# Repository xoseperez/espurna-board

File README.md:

View this project on [CADLAB.io](https://cadlab.io/node/890). 

# ESPurna Boards

## ESPurna-H

The ESPurna-H board is a custom ESP8266-based smart wall switch. It's singularity is that it's meant to be embedded into the wall behind a standard wall switch, replacing the mechanic switch with a wifi-enabled smart switch.

The board is based on the HLW8012 power monitor IC, the same the Sonoff POW uses.

It features:

* SPDT 10A relay with **NO and NC connections** brought out
* Connections for **external button and notification LED**
* HLW8012 chip for **power monitoring**
* 50x50mm low profile form factor to fit in the wall switch hole

## Bill of materials

|Item|Location(s)|Buy|Required|Optional <sup>H</sup>|CPU <sup>units</sup>|Total|Total <sup>H</sup>|
|---|---|---|---|---|---|---|---|
|Tinkerman ESPurna-H PCB||[OSH Park](https://oshpark.com/shared_projects/lxVzIaBY)|1||6.50€ <sup>3</sup>|6.50€||
|Ai-Thinker ESP12F|ESP-12|[Aliexpress](http://s.click.aliexpress.com/e/mUZjemI) / [Ebay](https://rover.ebay.com/rover/1/711-53200-19255-0/1?icep_id=114&ipn=icep&toolid=20004&campid=5338044841&mpre=http%3A%2F%2Fwww.ebay.com%2Fitm%2FESP8266-Remote-Serial-Port-WIFI-Transceiver-Wireless-Module-Esp-12F-AP-STA-%2F272408386985%3Fhash%3Ditem3f6cce1da9%3Ag%3ArywAAOSwZJBX-7RV)|1||2.10€ <sup>5</sup>|2.10€||
|Hi-Link HLK-PM01|HLK-PM01|[Aliexpress](http://s.click.aliexpress.com/e/yzVBurN) / [Ebay](https://rover.ebay.com/rover/1/711-53200-19255-0/1?icep_id=114&ipn=icep&toolid=20004&campid=5338044841&mpre=http%3A%2F%2Fwww.ebay.com%2Fitm%2FHousehold-Switch-Hlk-Pm01-Ac-Dc-220V-To-5V-Step-Down-Power-Supply-Module-New-I-F-%2F262910032033%3Fhash%3Ditem3d36a8b8a1%3Ag%3A8gwAAOSwal5YH5sM)|1||2.16€ <sup>5</sup>|2.16€||
|Songle SRD-05VDC-SL-C||[Aliexpress](http://s.click.aliexpress.com/e/6Au7qf2) / [Ebay](https://rover.ebay.com/rover/1/711-53200-19255-0/1?icep_id=114&ipn=icep&toolid=20004&campid=5338044841&mpre=http%3A%2F%2Fwww.ebay.com%2Fitm%2F1pcs-SRD-05VDC-SL-C-5V-DC-SONGLE-Power-Relay-SRD-05VDC-SL-C-PCB-Type-%2F262148054761%3Fhash%3Ditem3d093ddee9%3Ag%3A9VEAAOxykVNRq~7c)|1||0.39€ <sup>3</sup>|0.39€||
|AMS1117-3.3|IC1|[Aliexpress](http://s.click.aliexpress.com/e/uj6iuNv) / [Ebay](https://rover.ebay.com/rover/1/711-53200-19255-0/1?icep_id=114&ipn=icep&toolid=20004&campid=5338044841&mpre=http%3A%2F%2Fwww.ebay.com%2Fitm%2FNew-10pcs-AMS1117-LM1117-3-3V-1A-SOT-223-Voltage-Regulator-NT00206-Ship-Today-%2F112049991237%3Fhash%3Ditem1a16b32e45%3Ag%3AqV8AAOSw14xWNwXc)|1||0.03€ <sup>50</sup>|0.03€||
|HLW8012|IC4|[Aliexpress](http://s.click.aliexpress.com/e/Fq7URjq)||1|0.72€ <sup>20</sup>||0.72€|
|SF70E 73C thermal fuse|F1|[Aliexpress](http://s.click.aliexpress.com/e/Fq7MFIQ)|1||1.20€ <sup>5</sup>|1.20€||
|Fuse holder|FUSE|[Aliexpress](http://s.click.aliexpress.com/e/uBMfQzR)|1||0.06€ <sup>100</sup>|0.06€||
|500mA 250V fuse|FUSE|[Aliexpress](http://s.click.aliexpress.com/e/Rj2jYB6)|1||0.05€ <sup>100</sup>|0.05€||
|Varistor 270V|VARISTOR|[Aliexpress](http://s.click.aliexpress.com/e/bUjIA2Z)|1||0.18€ <sup>20</sup>|0.18€||
|Push button|RESET|[Aliexpress](http://s.click.aliexpress.com/e/Nzrf6aa)|1||0.02€ <sup>100</sup>|0.02€||
|1N4148 SMD Diode|D3|[Aliexpress](http://s.click.aliexpress.com/e/i2nayrB)|1||0.04€ <sup>100</sup>|0.04€||
|2N7002 SOT-223 N-Mosfet|Q2, Q3, Q4|[Aliexpress](http://s.click.aliexpress.com/e/yFQnA2J)|2|1|0.05€ <sup>50</sup>|0.10€|0.05€|
|10uF 0805 tantalum capacitor|C11, C12||2||0.01€ <sup>100</sup>|0.02€||
|100nF 0805 ceramic capacitor|C21, C22, C43, C45||2|2|0.01€ <sup>100</sup>|0.02€|0.02€|
|33nF 0805 ceramic capacitor|C41, C42|||2|0.01€ <sup>100</sup>||0.02€|
|1uF 0805 ceramic capacitor|C44|||1|0.01€ <sup>100</sup>||0.01€|
|0.001 2512 Ohm resistor|R41|[Aliexpress](http://s.click.aliexpress.com/e/fIaA6QB)||1|0.03€ <sup>10</sup>||0.03€|
|0 Ohm 1206 resistor|R42|[Aliexpress](http://s.click.aliexpress.com/e/jEAqfqb)||1|0.01€ <sup>500</sup>||0.01€|
|22Ohm 0805 resistor|R27||1||0.01€ <sup>100</sup>|0.01€||
|300Ohm 0805 resistor|R28||1||0.01€ <sup>100</sup>|0.01€||
|1KOhm 0805 resistor|R31, R43, R44, R50||1|3|0.01€ <sup>100</sup>|0.01€|0.03€|
|10KOhm 0805 resistor|R21, R22, R23, R24,<br />R25, R26, R32, R45,<br />R47, R49||7|3|0.01€ <sup>100</sup>|0.07€|0.03€|
|15KOhm 0805 resistor|R46, R48|||2|0.01€ <sup>100</sup>||0.02€|
|470KOhm 0805 resistor|R51, R52, R53, R54,<br />R55|||5|0.01€ <sup>100</sup>||0.05€|
|2 positions 5mm screw terminal||[Aliexpress](http://s.click.aliexpress.com/e/a2fqnM7)|1||0.06€ <sup>100</sup>|0.06€||
|3 positions 5mm screw terminal||[Aliexpress](http://s.click.aliexpress.com/e/Vjaa2RB)|1||0.07€ <sup>100</sup>|0.07€||
|5x2 position male header|||1||0.01€ <sup>100</sup>|0.01€||
|**Total**||||||13.11€|0.97€|

* (H) Optional, only required for power monitor.
* (units) Minimum quantity for the stated price.
* Prices are based on the cheapest option, usually Aliexpress.
* Check the schematic (image or eagle file) for relation between parts and values.

## Firmware

NOTE: PLEASE NOTE THAT IT IS A REQUIREMENT OF THE HLW8012 POWER MONITOR CHIP TO TIE THE POWER LINE TO THE CIRCUIT GROUND. THIS MEANS THAT YOU SHOULD NEVER EVER CONNECT THE BOARD GROUND TO YOUR COMPUTER WHILE CONNECTED TO MAINS. NEVER EVER FLASH THE BOARD WHILE CONNECTED TO MAINS!!

The ESPurna board is named after the [ESPurna firmware](https://bitbucket.org/xoseperez/espurna) which features:

* Support for multiple ESP8266-based boards (check list)
* Support for up to 5 different network configurations
* Support for different types of switches and different options (pulses, synchronization,..)
* **MQTT** enabled
* **Alexa integration** using the FauxmoESP Library
* **Domoticz** integration via MQTT
* **Home Assistant** integration via MQTT
* Support for different **sensors** (DHT22, DS18B20, HLW8012, current sensors, analog sensors,...)
* Fast asynchronous **HTTP Server**
* Backup and restore settings option
* Upgrade firmware from the web interface
* **REST API** (enable/disable from web interface)
* **Over-The-Air** (OTA) updates
* ... and much more

## Open Hardware

Hardware designs (schematics and CAD) files are licensed under the [Creative Commons Attribution-ShareAlike 3.0 Unported License](http://creativecommons.org/licenses/by-sa/3.0/) and follow the terms of the [OSHW (Open-source hardware) Statement of Principles 1.0.](http://freedomdefined.org/OSHW)

## Disclaimer

THIS PRODUCT IS TARGETED TO EXPERIENCED USERS AT THEIR OWN RISK. THIS PRODUCT IS MEANT TO BE USED PLUGGED TO MAINS AND IT REQUIRES A DEEP UNDERSTANDING OF THE PERILS OF HIGH VOLTAGE ON HUMAN LIFE.

TO THE FULLEST EXTENT PERMISSIBLE BY THE APPLICABLE LAW, I HEREBY DISCLAIM ANY AND ALL RESPONSIBILITY, RISK, LIABILITY AND DAMAGES ARISING OUT OF DEATH OR PERSONAL INJURY RESULTING FROM ASSEMBLY OR OPERATION OF THIS PRODUCT.

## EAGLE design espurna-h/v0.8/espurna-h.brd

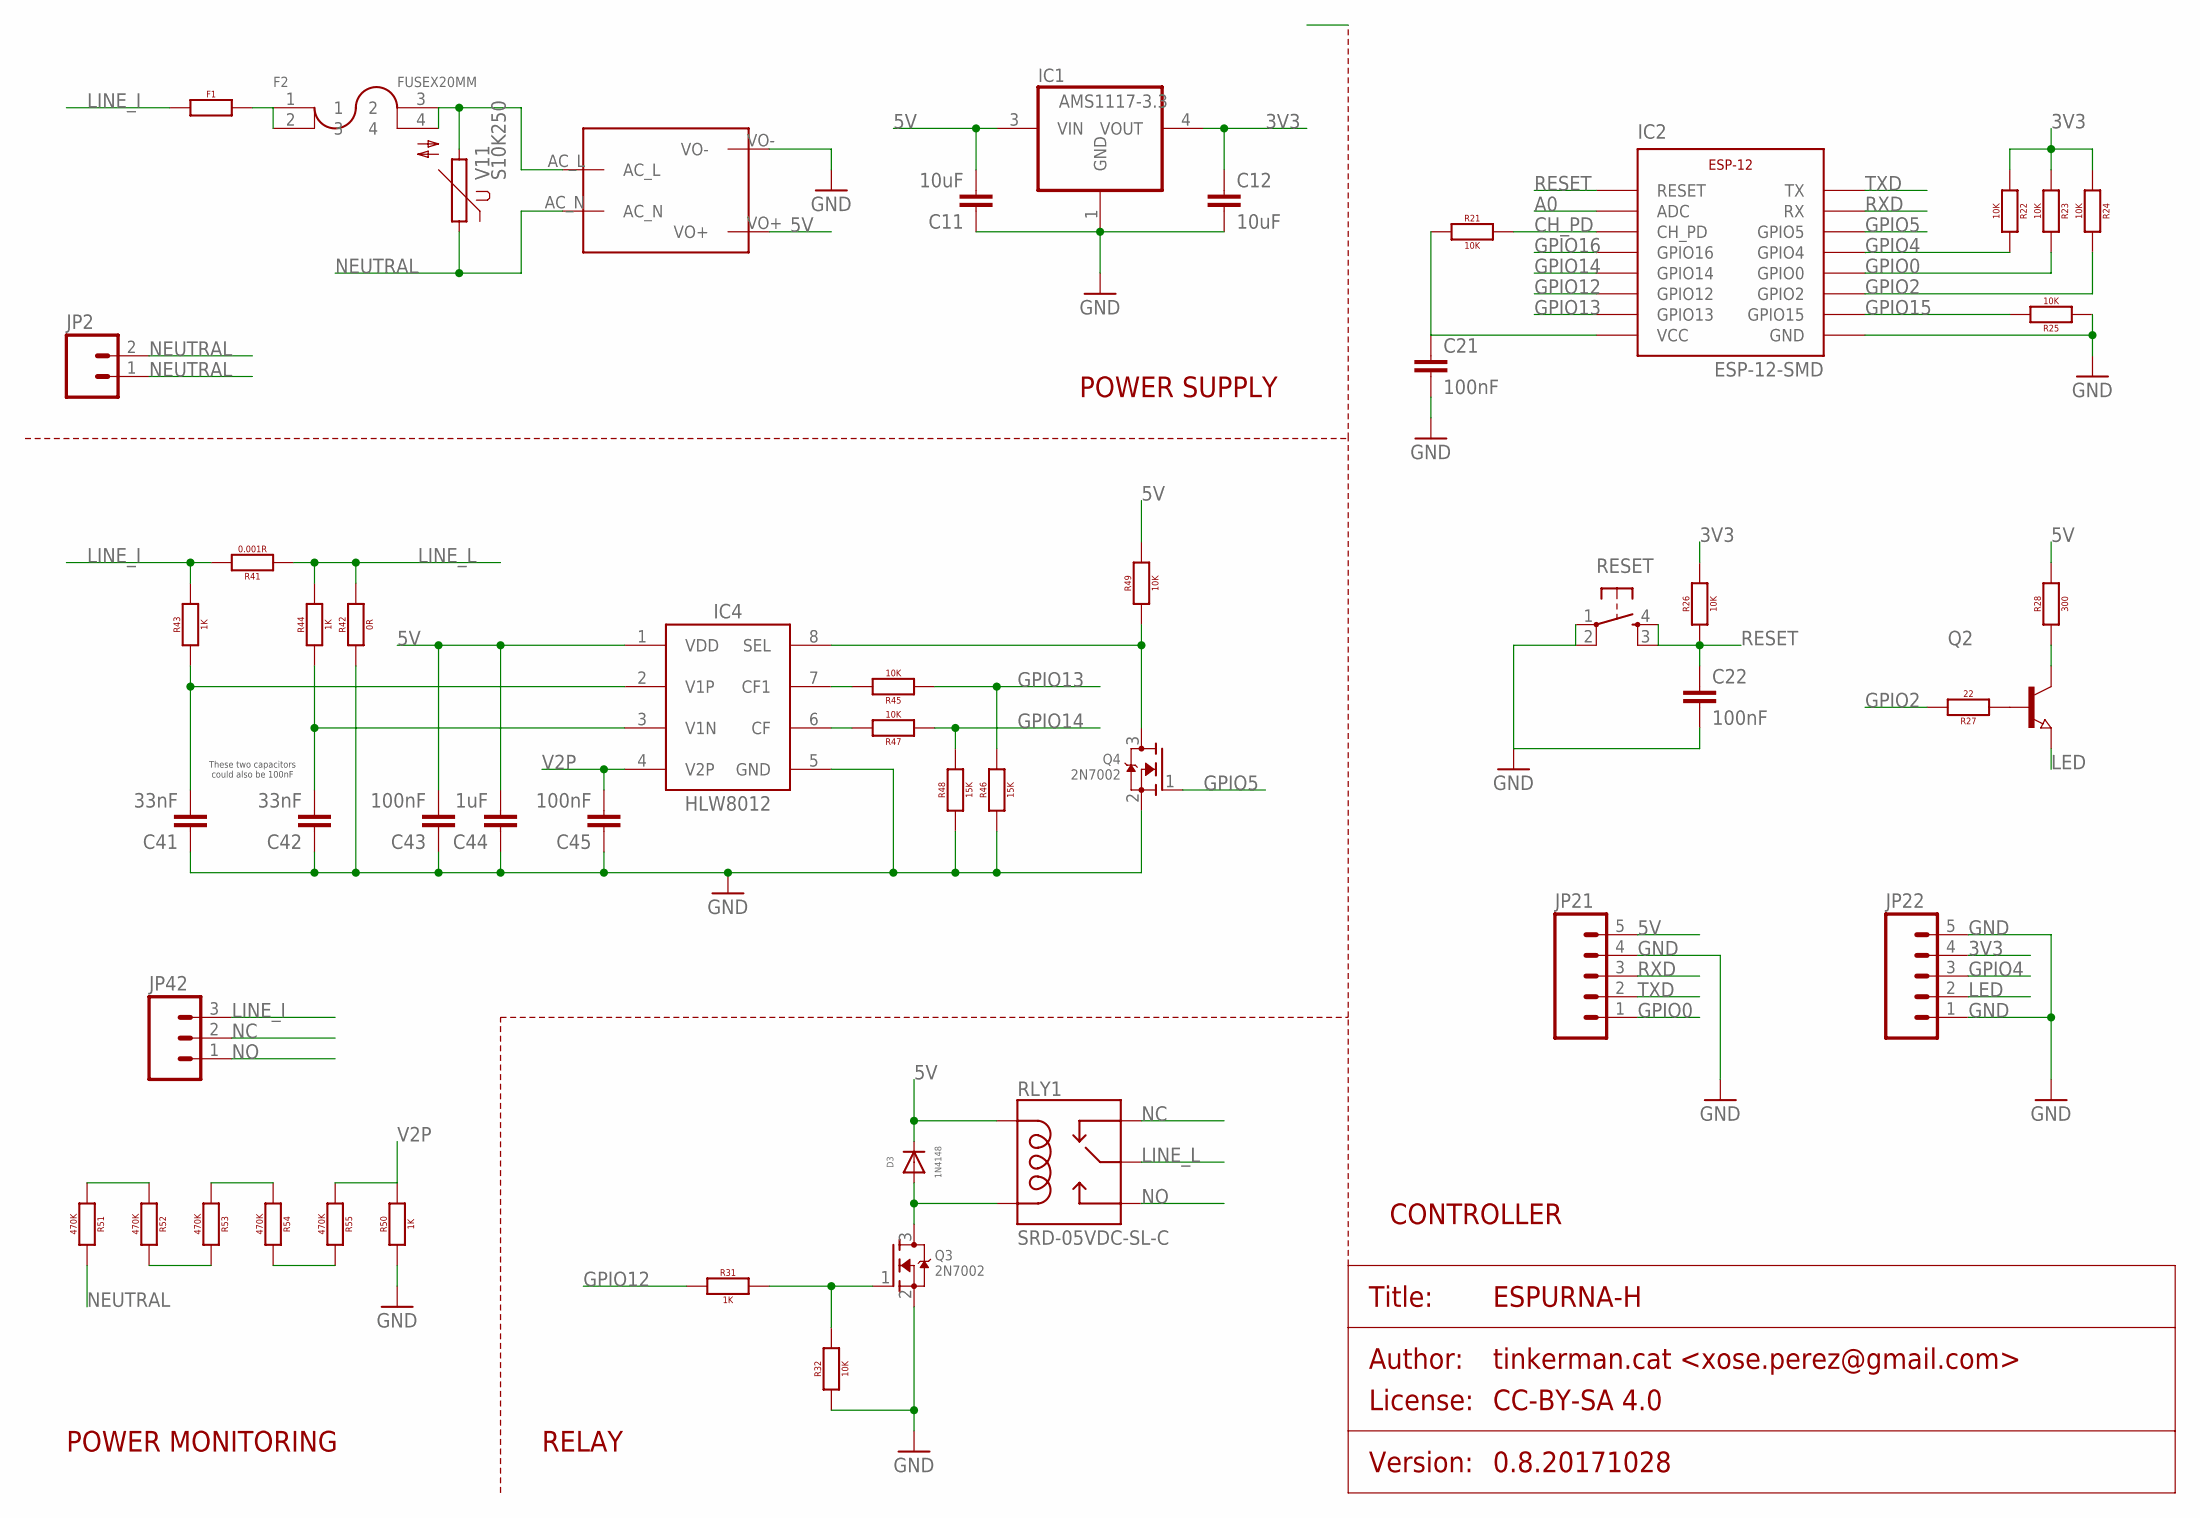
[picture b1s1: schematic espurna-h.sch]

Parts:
C11, C12: 10uF; 0805
C21, C22, C43, C45: 100nF; 0805
C41, C42: 33nF; 0805
C44: 1uF; 0805
D3: 1N4148; SOD80
F1: THERMALFUSE0.4; AXIAL-0.4
F2: FUSEX20MM; FUSE_5MM
IC1: AMS1117-3.3; SOT223
IC2: ESP-12-SMD
IC4: HLW8012; SOP8
JP2: M02200MIL; SCREWTERMINAL-200MIL-2
JP21, JP22: M05PTH; 1X05
JP42: M03200MIL; SCREWTERMINAL-200MIL-3
Q2: NPN-TRANSISTOR_SOT23; SOT23
Q3, Q4: 2N7002; SOT23
R21, R22, R23, R24, R25, R26, R32, R45, R47, R49: 10K; 0805
R27: 22; 0805
R28: 300; 0805
R31, R43, R44, R50: 1K; 0805
R41: 0.001R; 2512
R42: 0R; 1206
R46, R48: 15K; 0805
R51, R52, R53, R54, R55: 470K; 0805
RESET: TACTILE_BUTTON_SMD; TACTILE-BUTTON-SMD
RLY1: SRD-05VDC-SL-C; SRD-5VDC-SL-C
U$1: MAINS_CONVERTERS; HLK-PM01
V11: S10K250

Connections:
3V3: C12.1, C21.1, IC1.4 (VOUT), IC2.VCC, JP22.4, R21.1, R22.1, R23.1, R24.1, R26.2
5V: C11.2, C43.2, C44.2, D3.2 (C), IC1.3 (VIN), IC4.1 (VDD), JP21.5, R28.2, R49.2, RLY1.COIL1, U$1.VO+
A0: IC2.ADC
CH_PD: IC2.CH_PD, R21.2
GND: C11.1, C12.2, C21.2, C22.2, C41.1, C42.1, C43.1, C44.1, C45.1, IC1.1 (GND), IC2.GND, IC4.5 (GND), JP21.4, JP22.1, JP22.5, Q3.2 (S), Q4.2 (S), R25.1, R32.1, R42.1, R46.1, R48.1, R50.1, RESET.1 (SWA1), RESET.2 (SWB1), U$1.VO-
GPIO0: IC2.GPIO0, JP21.1, R23.2
GPIO2: IC2.GPIO2, R24.2, R27.2
GPIO4: IC2.GPIO4, JP22.3, R22.2
GPIO5: IC2.GPIO5, Q4.1 (G)
GPIO12: IC2.GPIO12, R31.1
GPIO13: IC2.GPIO13, R45.1, R46.2
GPIO14: IC2.GPIO14, R47.1, R48.2
GPIO15: IC2.GPIO15, R25.2
GPIO16: IC2.GPIO16
LED: JP22.2, Q2.2 (E)
LINE_I: F1.P$1 (1), JP42.3, R41.2, R43.2
LINE_L: R41.1, R42.2, R44.2, RLY1.COMMON (MAIN)
LINE_P: F2.3 (2), F2.4, U$1.AC_L, V11.2
unnamed: Q2.3 (C), R28.1
unnamed: Q2.1 (B), R27.1
unnamed: D3.1 (A), Q3.3 (D), RLY1.COIL2
unnamed: Q3.1 (G), R31.2, R32.2
unnamed: R51.1, R52.1
unnamed: F1.P$2 (2), F2.1, F2.2 (3)
unnamed: R52.2, R53.2
unnamed: IC4.8 (SEL), Q4.3 (D), R49.1
unnamed: IC4.7 (CF1), R45.2
unnamed: C41.2, IC4.2 (V1P), R43.1
unnamed: IC4.6 (CF), R47.2
unnamed: C42.2, IC4.3 (V1N), R44.1
unnamed: R53.1, R54.1
unnamed: R54.2, R55.2
NC: JP42.2, RLY1.CLOSED (NC)
NEUTRAL: JP2.1, JP2.2, R51.2, U$1.AC_N, V11.1
NO: JP42.1, RLY1.OPEN (NO)
RESET: C22.1, IC2.RESET, R26.1, RESET.3 (SWB2), RESET.4 (SWA2)
RXD: IC2.RX, JP21.3
TXD: IC2.TX, JP21.2
V2P: C45.2, IC4.4 (V2P), R50.2, R55.1

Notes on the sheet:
POWER SUPPLY
RELAY
CONTROLLER
POWER MONITORING
These two capacitors could also be 100nF

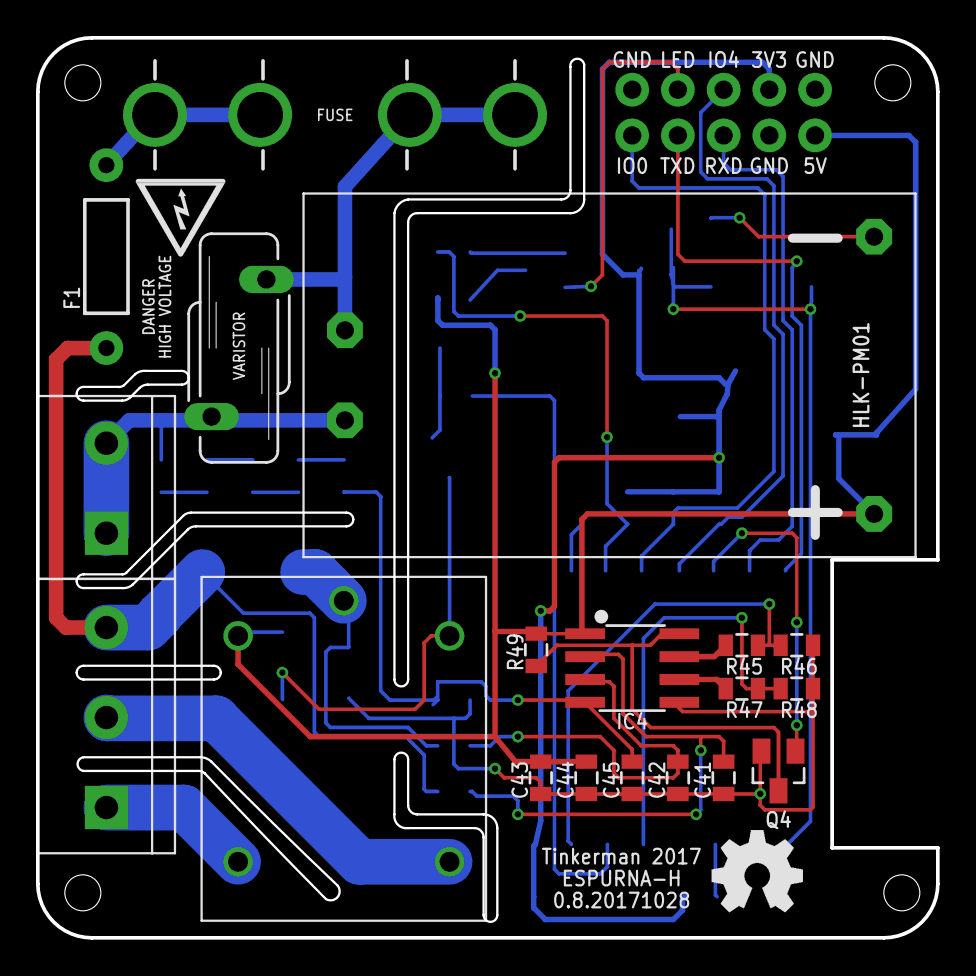
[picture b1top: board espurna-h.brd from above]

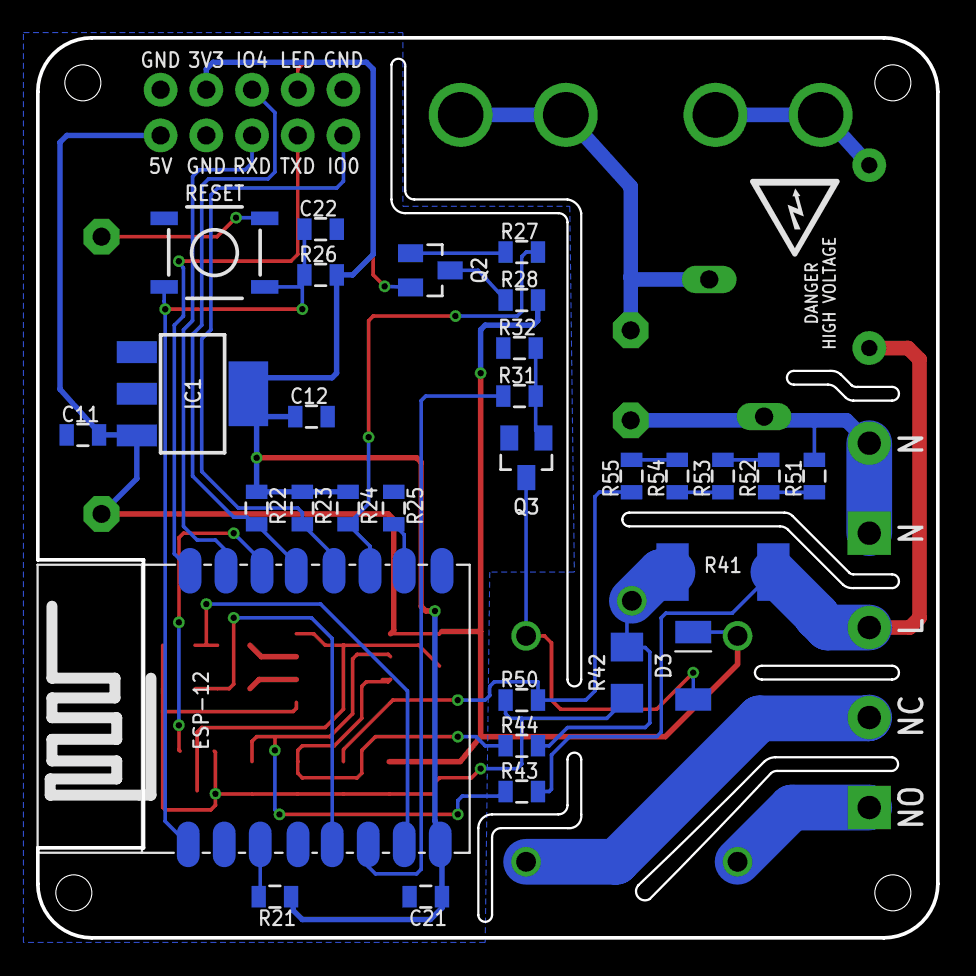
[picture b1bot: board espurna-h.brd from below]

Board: 2 copper layers, 50.0 x 50.0 mm, 55 parts (30 on the bottom side), 37 nets.

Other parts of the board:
U$2, U$3, U$4, U$5: HOLE_M2_WIDE

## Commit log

2017-04-07 Fix BOM table
2017-04-07 Updated BOM
2017-04-07 Licensed CC-BY-SA 3.0
2017-07-04 Swapped GPIO2 and GPIO5 to avoid the module LED to change with HLW8012 SEL pin value
2017-07-04 Relocate header window in base 3D model
2017-07-04 Change varistor symbol, added thermal fuse, change measurement point
2017-07-04 Added v0.6 shematic image
2017-09-13 Save eagle files for v0.6
2017-09-13 Separate power from load. Wire
2017-09-14 Version 0.7.20170913
2017-10-09 Freeze 0.7
2017-10-29 ESPurna H version 0.8.20171028
2017-10-29 ESPurna Board 0.8
2018-04-16 Backlink to CADLAB.io has been added.

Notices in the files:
espurna-h/espurna-h.sch:
PROJECT_LICENSE: CC-BY-SA 4.0
parts and their libraries:
SparkFun-Aesthetics: Licensing: Creative Commons ShareAlike 4.0 International - https://creativecommons.org/licenses/by-sa/4.0
